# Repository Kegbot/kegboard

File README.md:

# Kegboard

Kegboard is the kegerator controller firmware from the [Kegbot][kegbot] project.
It reads flow meters, temperature sensors, and auth tokens, drives valves and
relays, and reports pours to a [Kegbot Server][kegbot-server].

This is **Kegboard v4**, a ground-up rewrite for **ESP32** built on
[ESPHome][esphome].

> **Looking for the Arduino version?** The v2/v3 firmware lives on the
> [`arduino`](https://github.com/Kegbot/kegboard/tree/arduino) branch. It is
> feature-frozen and does not speak the same protocol as this one.

**[📖 Documentation](https://docs.kegbot.org/projects/kegboard)** — overview,
operating modes, installation, wiring, configuration, and the protocol specs.
Sources in [`docs/`](docs/).

## What changed, and why

The old Kegboard was a dumb sensor pipe: it streamed raw tick counts over USB
serial, and a host daemon (`kegbot-pycore`) assembled those ticks into pours and
posted them to the server. That meant a cable, a always-on host, and a lost pour
whenever the host was down.

Kegboard v4 is a networked appliance:

- **Pours are assembled on the device.** The board detects the start and end
  of a pour, applies its own calibration, and reports a finished pour with an
  authoritative `volume_ml`.
- **One simple protocol.** Everything is JSON batches to a single endpoint
  (`POST /kegboard-event`), specified in
  [docs/kegboard-event-protocol.md](docs/kegboard-event-protocol.md) with
  normative JSON Schemas. Any server can implement it.
- **Outages are survivable.** Events queue and deliver late with correct
  timestamps — even on a board whose clock never synced — and retries can
  never create a duplicate drink.
- **No API keys to carry around.** An unprovisioned board shows up on the
  server dashboard by name; click allow and it provisions itself.
- **No `kegbot-pycore`, no USB cable.** WiFi and HTTP.
- **It's ESPHome.** Adding a display, a pressure sensor, a second thermometer,
  or a different RFID reader is YAML you write, not a firmware release we ship.

## Status

Early. Under active construction — see the table below.

| Area | State |
|---|---|
| Core logic (pour detection, event protocol, grants) | Done, unit tested |
| `kegboard` hub + `kegboard_meter` | Done |
| `kegboard_reporter` (event protocol, pairing, commands) | Done |
| `kegboard_auth` (server-decided grants, local mode) | Done |
| Temperature via stock `dallas_temp` | Works |
| Relays with watchdog, buzzer, flow LEDs | Done |
| Auth readers (RFID, iButton) | Done |
| Server implementing the protocol | In progress (kegbot-server) |
| Prebuilt binaries + web installer | Planned |

Nothing has been validated against real hardware and a live Kegbot Server yet.

Reporting is **HTTP only** for now. MQTT, BLE, and WebSocket transports are
planned.

## Configuration

A minimal two-tap board reporting to a server:

```yaml
external_components:
  - source: github://Kegbot/kegboard@main

kegboard:
  id: kb

kegboard_meter:
  - id: flow0
    pin: GPIO4
    index: 0
    total:
      name: Tap 1 Ticks
    pouring:
      name: Tap 1 Pouring

kegboard_reporter:
  reporting_url: !secret kegboard_reporting_url
  meters: [flow0]
```

See `examples/` for complete configs, and `boards/` for pin maps.

### `kegboard`

| Option | Default | Notes |
|---|---|---|
| `serial_number` | `kegboard-<mac>` | Device identity in the protocol. Set explicitly to adopt a replaced board's identity. |

### `kegboard_meter`

| Option | Default | Notes |
|---|---|---|
| `pin` | required | Meter input. Pulled up internally; counts falling edges. |
| `meter_number` | `0` | The protocol's meter number: `(device, meter_number)` identifies a tap server-side. Must be unique per meter (validated at build). The YAML `id` is a config-internal reference and is never reported. |
| `ml_per_tick` | `0.185` | SwissFlow SF800 and clones (~5.4 ticks/mL). The device's calibration is authoritative: reported volume comes from this. |
| `debounce` | `1200us` | Matches the legacy firmware's filter. |
| `idle_timeout` | `10s` | Silence after which a pour is considered finished. |
| `min_pour_ticks` | `3` | Anything shorter is treated as a drip and discarded. |
| `max_pour_duration` | `5min` | Safety cutoff for a stuck meter; `0s` disables. |
| `report_interval` | `250ms` | Throttle for sensor updates during a pour. |
| `series_resolution` | `100ms` | Bucket width for the diagnostic tick series; `0s` disables. |

Optional entities: `total`, `volume`, `flow_rate`, `pouring`.
Triggers: `on_pour_start`, `on_pour_end` (with `ticks`, `volume_ml`, `duration_ms`).
Actions: `kegboard_meter.reset_total`, `.end_pour`, `.set_calibration`.

### `kegboard_reporter`

Speaks the [Kegboard Event Protocol](docs/kegboard-event-protocol.md).

| Option | Default | Notes |
|---|---|---|
| `reporting_url` | required | Full URL, path included, e.g. `https://kegbot.example.com/api/kegboard-event`. No credential is configured — the device provisions its own bearer token by pairing via the server dashboard, and it persists in flash. |
| `meters` | `[]` | Meters whose pours are reported. |
| `thermo_sensors` | `[]` | `sensor:`/`name:` pairs; any ESPHome sensor works. |
| `heartbeat_interval` | `60s` | Status event cadence; also bounds worst-case command latency. |
| `pour_update_interval` | `1s` | Live `pour_update` cadence; `0s` disables. |
| `retry_interval` | `30s` | Base for exponential backoff, capped at 5 min. |

Optional diagnostic entities: `queue_depth`, `dropped`. A non-zero `dropped`
means events were lost and is worth alerting on.

### `kegboard_auth`

Applies [authenticated pouring](docs/authenticated-pouring.md): per-meter
grants, decided by the server (or locally), driving valve toggles and pour
attribution.

| Option | Default | Notes |
|---|---|---|
| `mode` | `server` | `server`: every token presentment is decided by the server, which chooses the meters, user, and duration. `local`: every token pours as guest, serverlessly. |
| `gates` | `[]` | `meter:` plus optional `toggle:` (valve relay). A gate without a toggle gets attribution only. |
| `offline_policy` | `deny` | Token presented while the server is unreachable: `deny`, or `guest` (attribution only — never opens valves). |
| `max_grant_duration` | `5min` | Device-side clamp on server-issued grants: the final bound on valve-open time. |
| `local_grant_duration` | `30s` | Grant length in `local` mode and for offline-guest grants. |

Actions: `kegboard_auth.token_attached` / `.token_detached` (`device`,
`token`), `.revoke`. Condition: `.is_authorized`. Triggers: `on_authorized`
(`user`), `on_denied` (`reason`), `on_revoked`. Optional entities:
`authorized`, `user`.

### `kegboard_onewire`

iButton presence on a 1-Wire bus — ESPHome's `one_wire` enumerates devices but
has no arrive/leave events. Triggers `on_token_attached` and
`on_token_detached` with the ROM code as hex.

`max_missed_searches` (default `4`) is how many consecutive misses before a
detach is reported. A held iButton makes intermittent contact, so reporting on
the first miss would make it flap several times a second.

### Relays and buzzer

`packages/relays.yaml` and `packages/buzzer.yaml` are plain YAML over stock
components. The relay watchdog is worth keeping from the AVR firmware: a relay
left on is usually a valve held open, so each one switches itself off after
`relay_watchdog_timeout` (default `10s`) unless something turns it on again.

## Repository layout

```
components/     ESPHome external components (this repo is the component source)
  kegboard/     Hub component + the framework-agnostic core (see CORE.md)
  kegboard_meter/     Flow meter and pour detection
  kegboard_reporter/  Event protocol client (batching, pairing, commands)
  kegboard_auth/      Per-meter authorization
  kegboard_onewire/   iButton presence
packages/       Composable YAML users include
boards/         Pin maps per target board
docs/           Manual + protocol specifications
schemas/        Normative JSON Schemas for the protocol
examples/       Worked configurations
tests/core/     Host unit tests -- plain g++, no hardware, no toolchain
script/         CI helpers
```

## Development

Host unit tests for the core logic need nothing but a C++ compiler:

```console
$ make -C tests/core
$ make -C tests/core STRICT=1   # warnings as errors, as CI runs it
```

Build output is scoped by OS and architecture (`build/Darwin-arm64/`, etc.), so
a checkout shared between a host and a container or VM won't hand one
platform's binaries to the other.

Formatting and lint mirror ESPHome's own conventions, since these components
compile into ESPHome's tree:

```console
$ pip install pre-commit && pre-commit install
$ pre-commit run --all-files
```

The manual is a Sphinx project in `docs/`, published at
[docs.kegbot.org/projects/kegboard](https://docs.kegbot.org/projects/kegboard).
Its toolchain is managed by [uv](https://docs.astral.sh/uv/), synced
automatically on first use:

```console
$ make -C docs html          # output in docs/_build/html/
$ make -C docs livehtml      # live-rebuild server while editing
```

## Simulator

`tools/kegboard-sim.py` is a TUI kegboard for developing receivers without
hardware. It speaks the full protocol — pairing, batching, `age_ms`,
commands, dedup — and validates every outgoing batch against the schemas, so
it cannot teach a server the wrong protocol.

```console
$ uv run tools/kegboard-sim.py http://localhost:8000/kegboard-event
```

Single keys drive it: pour a beer (with live `pour_update`s), toggle
temperature logging, present preset tokens (including an unknown fob and a
presence-style iButton), kill the heartbeat so your server's liveness check
can notice, go offline to build a backlog that delivers late with correct
ages, replay the last batch verbatim to exercise dedup, send an
unknown event type, and reboot to reset `boot_id`.

## Debugging

The reporter logs one line per delivery at `DEBUG` (status, event count,
bytes). To see the actual protocol traffic — every request and response body,
including `pour_update`s while beer is flowing — raise its log level to
`VERY_VERBOSE`:

```yaml
logger:
  logs:
    kegboard_reporter: VERY_VERBOSE
```

Then attach with `esphome logs <config>.yaml`. Two notes:

- `VERY_VERBOSE` lines are compiled out at default log levels, so production
  builds pay nothing for this machinery.
- The logger truncates lines to its buffer (default 512 bytes); a full batch
  body will clip. Add `logger: { tx_buffer_size: 2048 }` if that bites.

## Hardware notes

**ESP32 GPIOs are not 5 V tolerant.** Most beer flow meters are open-collector
hall-effect sensors, which are safe on a 3.3 V pull-up because they only ever
pull the line to ground. Meters with a push-pull 5 V output will damage the
ESP32 and need a level shifter or divider. Check your meter before wiring it.

## History

Kegboard was created in 2004 and has received several major updates over the
years:

- **v1 (2004)** — PIC16-based, written in the JAL programming language.
- **v2 (~2009)** — rewritten for Arduino, introducing the KBSP serial
  protocol.
- **v3 (2014)** — the Kegboard Pro Mini, a fully-assembled Arduino-based
  board.
- **v4 (2026)** — this ground-up ESP32 rewrite on ESPHome.

## License and copyright

Kegboard v4 is offered under the **MIT** license, matching the rest of the
Kegbot project; see `LICENSE.txt`.

Two notes on what that does and doesn't cover:

- **Built firmware images are GPLv3.** ESPHome's C++ runtime is GPLv3, and a
  compiled Kegboard image links against it. MIT is GPL-compatible, so this is
  fine and is how ESPHome external components normally work — but if you
  distribute binaries, you are distributing GPLv3 binaries. The source in this
  repository remains MIT and is reusable as such.
- **The `arduino` branch is still GPLv2-or-later.** The legacy AVR firmware was
  written under that license and had outside contributors; nothing here
  relicenses it.

Copyright 2003-2026 The Kegbot Project Contributors <info@kegbot.org>

[kegbot]: https://kegbot.org/
[kegbot-server]: https://github.com/Kegbot/kegbot-server
[esphome]: https://esphome.io/

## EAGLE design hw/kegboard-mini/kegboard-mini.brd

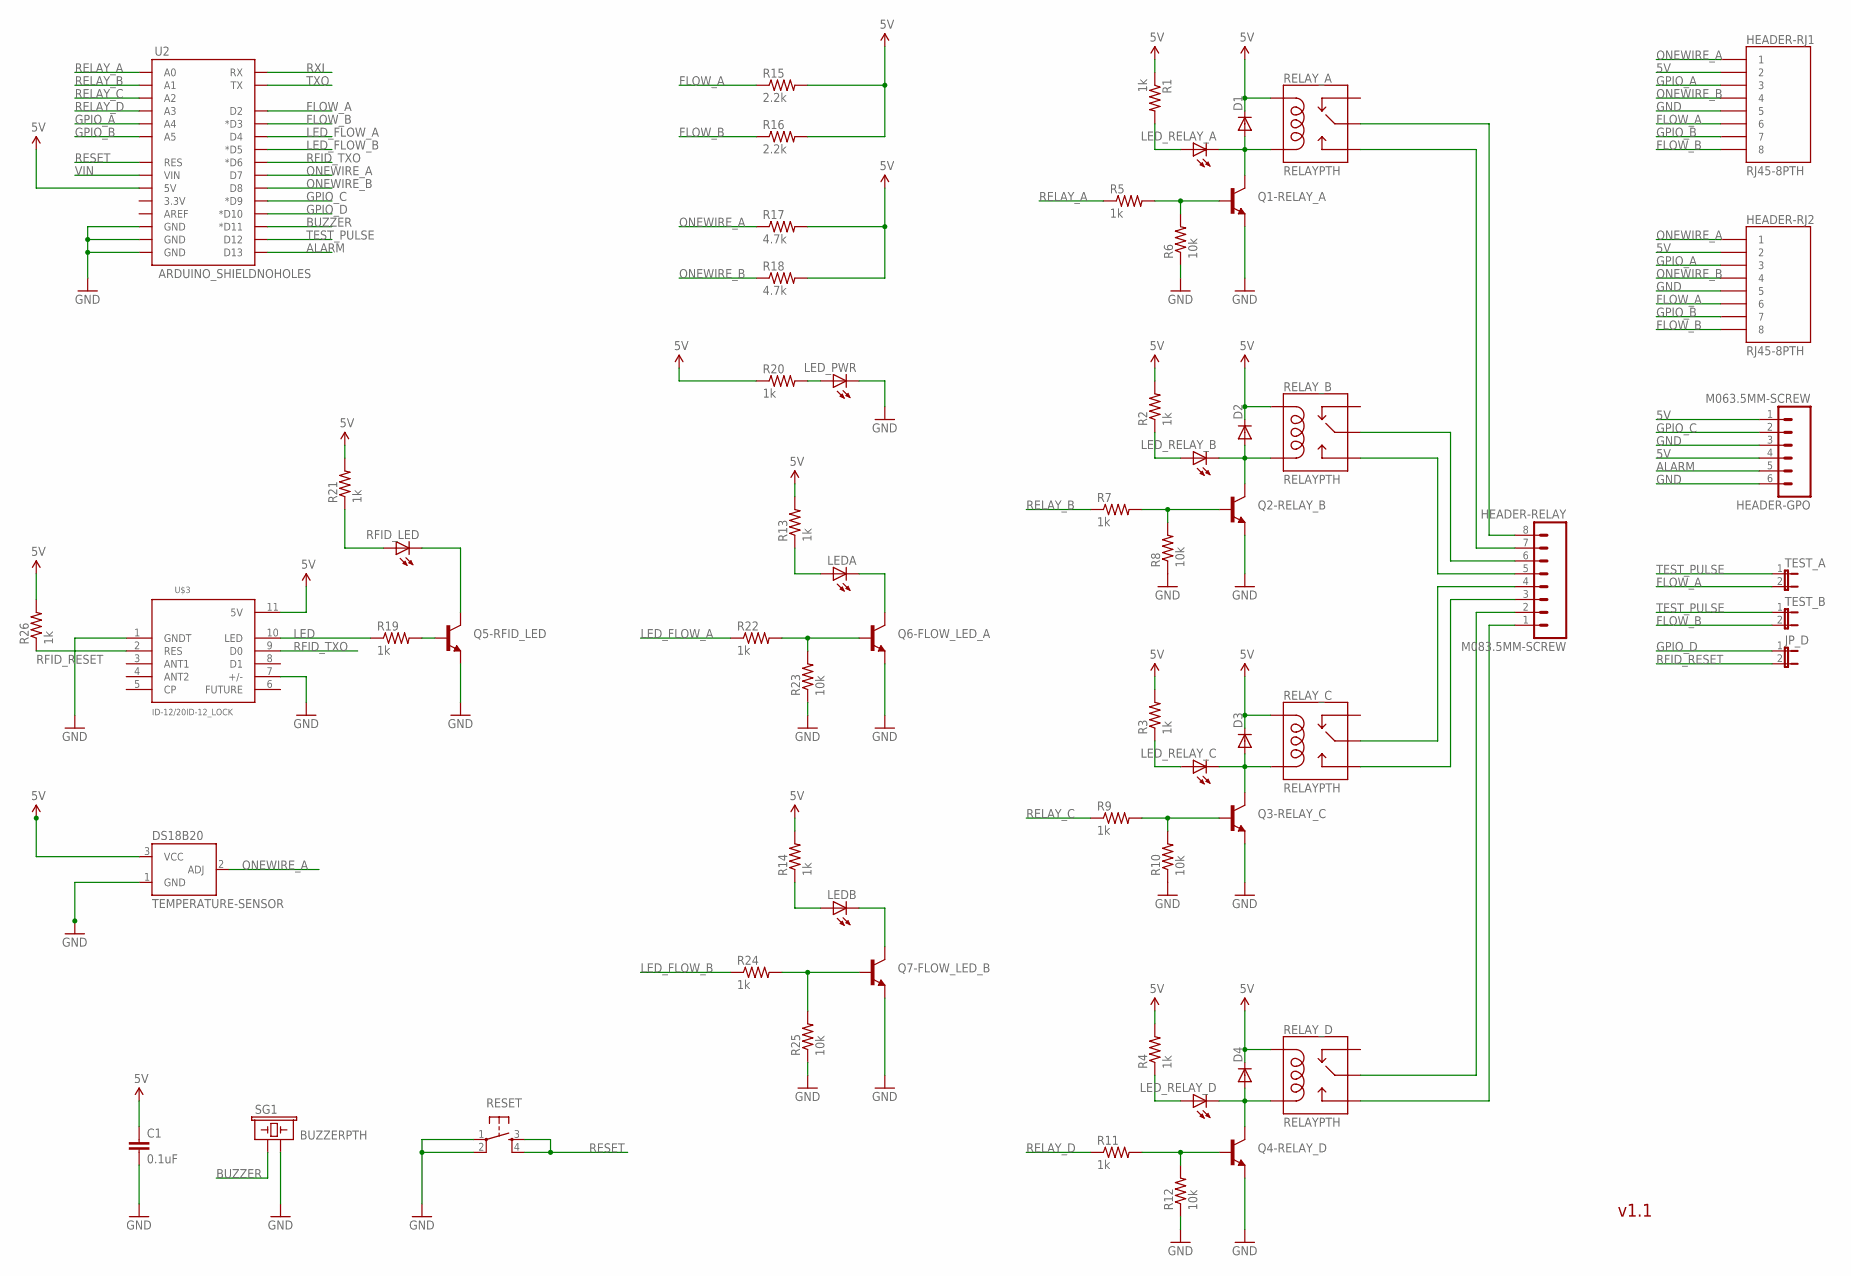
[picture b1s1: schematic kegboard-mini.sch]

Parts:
C1: 0.1uF; CAP-PTH-SMALL
D1, D2, D3, D4: DIODE1N4148; DIODE-1N4148
DS18B20: TEMPERATURE-SENSOR; TO-92
HEADER-GPO: M063.5MM-SCREW; SCREWTERMINAL-3.5MM-6
HEADER-RELAY: M083.5MM-SCREW; SCREWTERMINAL-3.5MM-8
HEADER-RJ1, HEADER-RJ2: RJ45-8PTH; RJ45-8
JP_D: JUMPER-2PTH; 1X02
LEDA: LED3MM
LEDB: LED3MM
LED_PWR: LED3MM
LED_RELAY_A: LED3MM
LED_RELAY_B: LED3MM
LED_RELAY_C: LED3MM
LED_RELAY_D: LED3MM
Q1-RELAY_A, Q2-RELAY_B, Q3-RELAY_C, Q4-RELAY_D, Q5-RFID_LED, Q6-FLOW_LED_A, Q7-FLOW_LED_B: TRANSISTOR_NPNTO92; TO-92
R1, R2, R3, R4, R5, R7, R9, R11, R13, R14, R19, R20, R21, R22, R24, R26: 1k; AXIAL-0.3
R6, R8, R10, R12, R23, R25: 10k; AXIAL-0.3
R15, R16: 2.2k; AXIAL-0.3
R17, R18: 4.7k; AXIAL-0.3
RELAY_A: RELAYPTH; RELAY-G5Q
RELAY_B: RELAYPTH; RELAY-G5Q
RELAY_C: RELAYPTH; RELAY-G5Q
RELAY_D: RELAYPTH; RELAY-G5Q
RESET: TAC_SWITCHPTH; TACTILE-PTH
RFID_LED: LED3MM
SG1: BUZZERPTH; BUZZER-12MM
TEST_A: JUMPER-2PTH; 1X02
TEST_B: JUMPER-2PTH; 1X02
U2: ARDUINO_SHIELDNOHOLES; DUEMILANOVE_SHIELD_NOHOLES
U$3: ID-12/20ID-12_LOCK; ID-12_LOCK

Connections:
5V: C1.1, D1.C, D2.C, D3.C, D4.C, DS18B20.3 (VCC), HEADER-GPO.1, HEADER-GPO.4, HEADER-RJ1.2, HEADER-RJ2.2, R1.P$1 (1), R2.P$2 (2), R3.P$2 (2), R4.P$2 (2), R13.P$2 (2), R14.P$2 (2), R15.P$2 (2), R16.P$2 (2), R17.P$2 (2), R18.P$2 (2), R20.P$1 (1), R21.P$2 (2), R26.P$2 (2), RELAY_A.5 (COIL1), RELAY_B.5 (COIL1), RELAY_C.5 (COIL1), RELAY_D.5 (COIL1), U2.5V, U$3.11 (5V)
ALARM: HEADER-GPO.5, U2.D13
BUZZER: SG1.+ (1), U2.D11 (*D11)
FLOW_A: HEADER-RJ1.6, HEADER-RJ2.6, R15.P$1 (1), TEST_A.2, U2.D2
FLOW_B: HEADER-RJ1.8, HEADER-RJ2.8, R16.P$1 (1), TEST_B.2, U2.D3 (*D3)
GND: C1.2, DS18B20.1 (GND), HEADER-GPO.3, HEADER-GPO.6, HEADER-RJ1.5, HEADER-RJ2.5, LED_PWR.K (C), Q1-RELAY_A.1 (E), Q2-RELAY_B.1 (E), Q3-RELAY_C.1 (E), Q4-RELAY_D.1 (E), Q5-RFID_LED.1 (E), Q6-FLOW_LED_A.1 (E), Q7-FLOW_LED_B.1 (E), R6.P$1 (1), R8.P$1 (1), R10.P$1 (1), R12.P$1 (1), R23.P$1 (1), R25.P$1 (1), RESET.1, RESET.2, SG1.- (2), U2.GND@0 (GND), U2.GND@1 (GND), U2.GND@2 (GND), U$3.1 (GNDT), U$3.7 (+/-)
GPIO_A: HEADER-RJ1.3, HEADER-RJ2.3, U2.A4
GPIO_B: HEADER-RJ1.7, HEADER-RJ2.7, U2.A5
GPIO_C: HEADER-GPO.2, U2.D9 (*D9)
GPIO_D: JP_D.1, U2.D10 (*D10)
LED: R19.P$1 (1), U$3.10 (LED)
LED_FLOW_A: R22.P$1 (1), U2.D4
LED_FLOW_B: R24.P$1 (1), U2.D5 (*D5)
unnamed: LED_RELAY_A.A, R1.P$2 (2)
unnamed: Q2-RELAY_B.2 (B), R7.P$2 (2), R8.P$2 (2)
unnamed: Q1-RELAY_A.2 (B), R5.P$2 (2), R6.P$2 (2)
unnamed: Q3-RELAY_C.2 (B), R9.P$2 (2), R10.P$2 (2)
unnamed: LED_RELAY_C.A, R3.P$1 (1)
unnamed: Q4-RELAY_D.2 (B), R11.P$2 (2), R12.P$2 (2)
unnamed: LED_RELAY_B.A, R2.P$1 (1)
unnamed: LEDB.K (C), Q7-FLOW_LED_B.3 (C)
unnamed: LEDA.K (C), Q6-FLOW_LED_A.3 (C)
unnamed: D1.A, LED_RELAY_A.K (C), Q1-RELAY_A.3 (C), RELAY_A.1 (COIL2)
unnamed: LED_RELAY_D.A, R4.P$1 (1)
unnamed: D2.A, LED_RELAY_B.K (C), Q2-RELAY_B.3 (C), RELAY_B.1 (COIL2)
unnamed: LED_PWR.A, R20.P$2 (2)
unnamed: D3.A, LED_RELAY_C.K (C), Q3-RELAY_C.3 (C), RELAY_C.1 (COIL2)
unnamed: HEADER-RELAY.8, RELAY_A.2 (MAIN)
unnamed: D4.A, LED_RELAY_D.K (C), Q4-RELAY_D.3 (C), RELAY_D.1 (COIL2)
unnamed: Q5-RFID_LED.2 (B), R19.P$2 (2)
unnamed: R21.P$1 (1), RFID_LED.A
unnamed: Q5-RFID_LED.3 (C), RFID_LED.K (C)
unnamed: HEADER-RELAY.7, RELAY_A.3 (NO)
unnamed: HEADER-RELAY.6, RELAY_B.2 (MAIN)
unnamed: HEADER-RELAY.5, RELAY_B.3 (NO)
unnamed: HEADER-RELAY.4, RELAY_C.2 (MAIN)
unnamed: LEDA.A, R13.P$1 (1)
unnamed: HEADER-RELAY.3, RELAY_C.3 (NO)
unnamed: HEADER-RELAY.2, RELAY_D.2 (MAIN)
unnamed: HEADER-RELAY.1, RELAY_D.3 (NO)
unnamed: LEDB.A, R14.P$1 (1)
unnamed: Q6-FLOW_LED_A.2 (B), R22.P$2 (2), R23.P$2 (2)
unnamed: Q7-FLOW_LED_B.2 (B), R24.P$2 (2), R25.P$2 (2)
ONEWIRE_A: DS18B20.2 (ADJ), HEADER-RJ1.1, HEADER-RJ2.1, R17.P$1 (1), U2.D7
ONEWIRE_B: HEADER-RJ1.4, HEADER-RJ2.4, R18.P$1 (1), U2.D8
RELAY_A: R5.P$1 (1), U2.A0
RELAY_B: R7.P$1 (1), U2.A1
RELAY_C: R9.P$1 (1), U2.A2
RELAY_D: R11.P$1 (1), U2.A3
RESET: RESET.3, RESET.4, U2.RES
RFID_RESET: JP_D.2, R26.P$1 (1), U$3.2 (RES)
RFID_TXO: U2.D6 (*D6), U$3.9 (D0)
RXI: U2.RX
TEST_PULSE: TEST_A.1, TEST_B.1, U2.D12
TXO: U2.TX
VIN: U2.VIN

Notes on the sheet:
v1.1

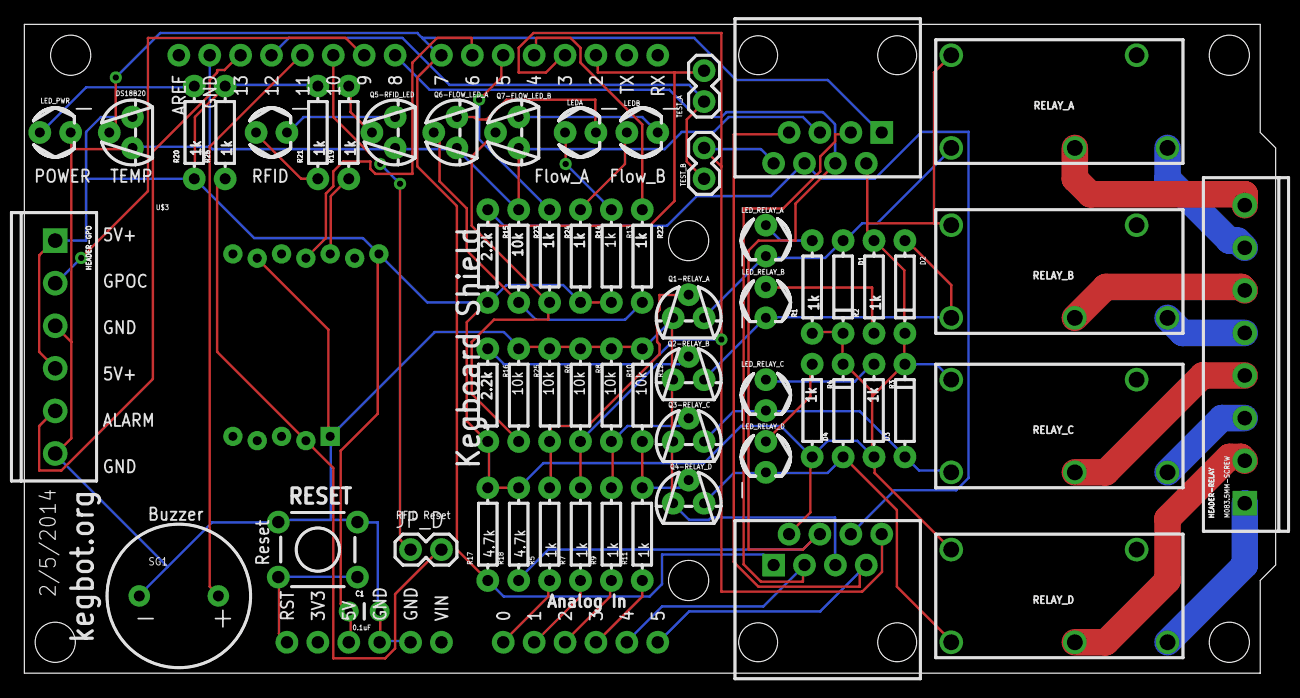
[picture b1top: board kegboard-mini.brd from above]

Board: 2 copper layers, 102.9 x 53.3 mm, 68 parts (0 on the bottom side), 53 nets.

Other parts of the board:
JP1, JP2, JP3, JP4, JP5, JP6: STAND-OFF

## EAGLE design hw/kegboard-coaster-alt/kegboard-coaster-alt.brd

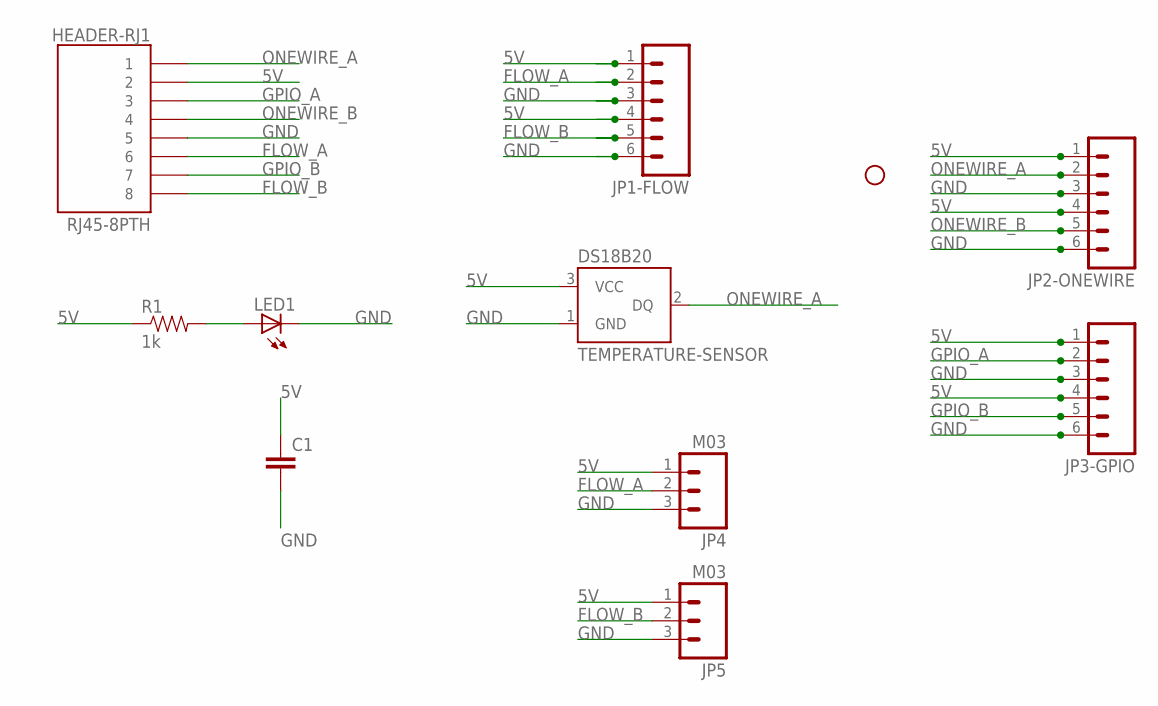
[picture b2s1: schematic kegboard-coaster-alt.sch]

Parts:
C1: CAPPTH2; CAP-PTH-SMALL2
HEADER-RJ1: RJ45-8PTH; RJ45-8
JP1-FLOW, JP2-ONEWIRE, JP3-GPIO: M063.5MM-6; SCREWTERMINAL-3.5MM-6
JP2: STAND-OFF
JP4, JP5: M03; 53324-0360
LED1: LED3MM
R1: 1k; AXIAL-0.3
U$1: TEMPERATURE-SENSOR; TO-92

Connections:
5V: C1.1, HEADER-RJ1.2, JP1-FLOW.1, JP1-FLOW.4, JP2-ONEWIRE.1, JP2-ONEWIRE.4, JP3-GPIO.1, JP3-GPIO.4, JP4.1, JP5.1, R1.P$1 (1), U$1.3 (VCC)
FLOW_A: HEADER-RJ1.6, JP1-FLOW.2, JP4.2
FLOW_B: HEADER-RJ1.8, JP1-FLOW.5, JP5.2
GND: C1.2, HEADER-RJ1.5, JP1-FLOW.3, JP1-FLOW.6, JP2-ONEWIRE.3, JP2-ONEWIRE.6, JP3-GPIO.3, JP3-GPIO.6, JP4.3, JP5.3, LED1.K (C), U$1.1 (GND)
GPIO_A: HEADER-RJ1.3, JP3-GPIO.2
GPIO_B: HEADER-RJ1.7, JP3-GPIO.5
unnamed: LED1.A, R1.P$2 (2)
ONEWIRE_A: HEADER-RJ1.1, JP2-ONEWIRE.2, U$1.2 (DQ)
ONEWIRE_B: HEADER-RJ1.4, JP2-ONEWIRE.5

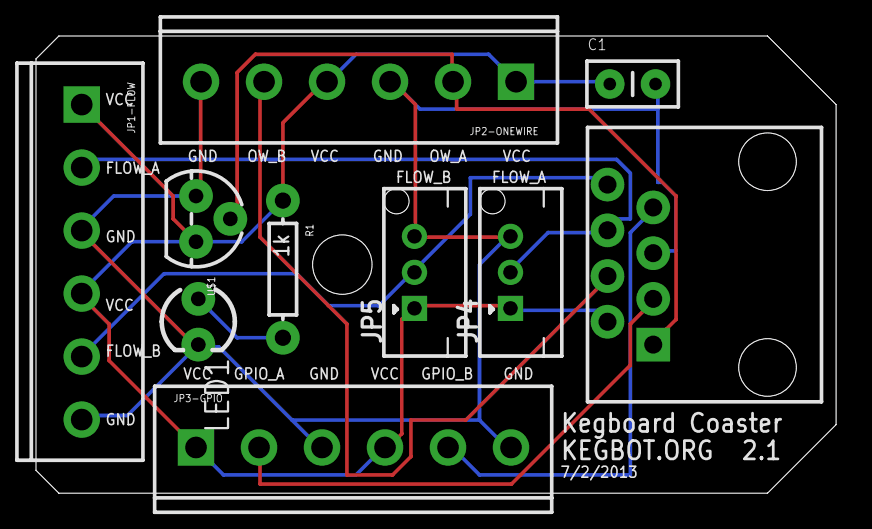
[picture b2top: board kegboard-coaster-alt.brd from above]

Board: 2 copper layers, 44.5 x 25.4 mm, 11 parts (0 on the bottom side), 9 nets.

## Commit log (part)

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2002-05-28 initial checkin
2006-04-02 - add kegboard source
2006-04-03 - adding original rs232_hw jal file, from: http://oase.uci.kun.nl/~mientki/pic/libs_hw/rs232_hw.html
    needs some modification to work with jpic registe defines
2006-04-03 - cleaned up kegboard.jal - added jpic comptabile pin/register definitions -- I must have inherited a bunch of weird naming conventions from JALss - added a Makefile
2006-04-03 - add Philip Pemberton's 1wire.jal library
2006-04-03 - deleting; accidentally submitted changed version
2006-04-03 - update to use jdelay (more portable)
2006-04-03 - added temperature support!
2006-04-03 - update to constantly push status (1x/second in normal case, 5x/second in flow) - added some untested procedures for printing as ascii :)
2006-04-03 - added init message
2006-04-04 - added human-readable output for all fields in the status packet! - changed command names to all be (a) a single ascii char, and (b) intuitive (ie 'F' to enable fridge, 'f' to disable) - TODO: board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
2012-03-31 Add option to force-set HUPCL on the serial port. Source: http://www.arduino.cc/cgi-bin/yabb2/YaBB.pl?num=1201441300
2012-03-31 Revert default baud rate to 115200bps.
2012-03-31 Add TODO.
2012-03-31 Many enhancements to kegboard3.
    - adds onewire support
    - created a non-delay()ing wrapper for ds18*20 sensors
    - temperature conversion now supported
    - adds start of TLV eeprom storage. untested, compiles.
    - many todos and cleanups remain
2012-03-31 Better idea: don't mess with HUPCL, instead just set the rate to 0.
2012-03-31 Add CRC-CCITT (Xmodem) checksum of flow data.
2012-03-31 Add command line makefile.
2012-03-31 Fix up Makefile defaults.
2012-03-31 Move hardware controller code out of pykeg.
2012-03-31 Enable weak internal pullups on flow pins.
2012-03-31 Kegboard updates: new command format, start handling rx commands.
    Still a work in progress.
2012-03-31 Rename project file to make arduino ide happy.
2012-03-31 Increase responsiveness of the main loop.
    This change removes the delay in the main loop; as a result, some operations are
    noticably more responsibe (eg OneWire presence events). Searches happen much
    more frequently as well.
    Changes selftest to report on a set interval (every 500ms), making it
    easier to use in testing situations.
2012-03-31 Fix serial packet output (missing preamble).
2012-03-31 Add 1-wire presence detect to kegboard; rework temperature sensing.
    Details:
    - One bus is now dedicated to temperature sensor (and no longer operates in
    onewire 'skip' mode); the other is now used for presence events.
    - A new KBSP message has been added for presence events, and pykeg side has
    been updated to parse this message. (Auth support for kegboard_daemon to be
    added later.)
2012-03-31 Move buzzer.c -> buzzer.cpp
2012-03-31 Fix temperature conversion.
    Add protocol version.
2012-03-31 Fix bug in OneWire::search.
    The condition where a device disappears mid-search was not handled correctly; as
    a result, a button removed mid search could end up being reported indefinitely.
    This could be easily reproduced by repeatedly searching & wiggling the iButton
    device physically on and off the bus.
    Misc whitespace/style cleanups.
2012-03-31 Snapshot of initial support for receiving command packets. Not yet tested.
2012-03-31 Remove dead eeprom code. Reimplement this later. Allocate pin for buzzer.
2012-03-31 Bug fix for onewire changes.
    Also adds support for DS18S20 temperature sensor.
2012-03-31 Fix build when OneWire is disabled (thanks Andrew!)
2012-03-31 DS1820 bugfix: Do not report '0' for a sensor that disappears mid-read.
2012-03-31 Print avr-size after building elf.
2012-03-31 Rename kegboard source tree to satisfy the wacky arduino IDE.
    Resolves issue #6.
2012-03-31 Whitespace cleanup.
2012-03-31 Fix CRC'ing of KBSP packets.
2012-03-31 Fix broken melody note.
2012-03-31 Whitespace/style cleanups.
2012-03-31 Initial support for Matrix-Orbital serial LCDs; rx packet bugfixes.
2012-03-31 Move boot melody data to PROGMEM, saving a few dozen bytes.
    Code and data sizes have significantly shrunk thanks to the past few
    optimizations.
    Output of /usr/bin/avr-size -C --mcu=atmega168 build-cli/kegboard-v3.elf
    At revision 602:
    AVR Memory Usage
    ----------------
2012-03-31 Kegboard: Experimental change to cache onewire device presence and report device absence.
    Written without access to AVR: needs to be tested. Also need update to kegboard
    daemon due to changed semantics of presence packet.
2012-03-31 Move buzzer constants to progrem memory, saving a few dozen bytes of RAM.
2012-03-31 Fix stupid offset error.
2012-03-31 Remove the global KegboardPacket used for serial output; instead, create it on demand.
2012-03-31 Change protocol_version field to firmware_version; set initial version to 4.
2012-03-31 Add relay on/off command support; clean up types.
2012-03-31 Small optimizations.
    - Compute crc inline while printing a packet.
    - Refactor handling of multi-byte integer values.
2012-03-31 Recover over 200 bytes of program data by removing _delay_ms.
    Also removes MelodyNote structure, to simplify storing melodies with PROGMEM.
2012-03-31 Update to kegboard firmware v5. Fixes issue with excessive tick reporting.
2012-03-31 Clean up onewire search to better match appnote flow chart.
    Check CRC before returning results.
2012-03-31 Fix status reporting.
2012-03-31 Use SoftwareSerial.
2012-03-31 kegboard-coaster: update pin breakouts.
2012-03-31 First draft of arduino carrier board (Eagle project files.)
2012-03-31 Update with changes from geoff culp (geoffculp@gmail.com).
2012-03-31 Update shield design.
    Changes:
    - now sized for / compatible with Arduino MEGA
    - supports up to 6 flow inputs
    - up to 6 RJ45 sockets
    - 4 output relay blocks
    - 4 general purpose output terminal blocks
2012-03-31 coaster: tweaks to layout; autorouted.
2012-03-31 First attempt at routing the relay section.
2012-03-31 Board updates; see ChangeLog.
2012-03-31 kegboard-coaster: tweaking things (see changelog)
2012-03-31 kegboard-mini: initial routing.
2012-03-31 Update to work with arduino-0018.
    Resolves issue #37.
2012-03-31 Add missing include.
2012-03-31 Update board and schematic.
2012-03-31 Split kegboard shield projects into "mega" and "mini" versions.
    The "mini" version is copied from kegboard.{brd,sch} at hg revision 794. The
    existing kegboard.{brd,sch} have been moved to kegboard-mega.{brd,sch}.
2012-03-31 kegboard: disable serial lcd by default.
2012-03-31 kegboard: various pcb board layout changes, see change log for details.
2012-03-31 kegboard: fix build error with arduino-0022 (issue #77).
    (thanks jared)
2012-03-31 kegboard: add the auth_token message.
    The new message type is similar to the existing `onewire_presence` message, but
    adds an additional string field for the auth device name.
    This should make it possible to add report new types of auth tokens from
    kegboard (eg rfid, magstripe) without needing to define a new message or change
    kegboard daemon.
2012-03-31 kegboard: remove dash from relay names for consistency with meters.
2012-03-31 kegboard: (hopefully final) updates & routing before initial production.
    Changes:
    - Removed XBee components, replaced with ID-20/ID-12 RFID sensor. I decided
    (or rather guessed) that the RFID sensor would be a more popular choice, and
    the XBee can probably be supported with an additional stackable shield.
    Like the XBee, this component is optional.
    - Moved the RJ-45 jacks to the back-left edge, rather than opposing back
2012-03-31 kegboard: Expand 'set_output' to support onboard kegboard relay's, flow led's
2012-03-31 kegboard: minor cleanup to makefile.
2012-03-31 kegboard: bump firmware version to 6.
2012-03-31 kegboard: update schematic.
    Changes:
    - Remove notch from upper left corner (thanks geoffc).
    - Add drill hole for arduino uno; rearrange and re-route a few components to
    accomodate (thanks geoffc).
    - Rerouted a trace that had been autorouted too close to the relay rails.
2012-03-31 Arduino.mk: update to version 0.4; add notice.
2012-03-31 kegboard: Add NewSoftSerial library.
2012-03-31 kegboard fw: s/KB_MESSAGE_TYPE/KBM/g
2012-03-31 kegboard: coaster updates (1/23 version)
2012-03-31 kegboard fw: trivial changes.
2012-03-31 Adding support for magnetic stripe cards and pin change interrupts
2012-03-31 kegboard: fix bug in previous commit.
    (Don't play the melody for disapperances.)
2012-03-31 Kegboard: Alternate coaster design. Larger pcb board size for screw terminals.
2012-03-31 Fix errant ifdef
2012-03-31 kegboard: add logo and bump date.
2012-03-31 kegboard: reverse ID12 endianness to match other readers; bump to fw v10.
2012-03-31 NewSoftSerial: convert to unix file format.
2012-03-31 kegboard: bump to fw version 9; update docs.
2012-03-31 kegboard: 8/8/2011 revision, with logo
2012-03-31 Reorganize as standalone package.
2012-03-31 kegboard: play melody *after* emitting auth packet.
    Melody playback uses delay(). That should be fixed, but in the meantime do the
    "real" work first.
2012-05-03 Rename kegboard.pde -> kegboard.ino for Arduino 1.0
2012-05-03 Update for Arduino SDK v1.0. Bump to rev 11.
2012-07-01 Rename src/ to arduino/
2012-07-02 Move Kegboard Python code into kegboard repository.
    New package is called "kegbot-kegboard".
    Origin:
    URL: https://github.com/Kegbot/kegbot
    Commit: a0fc59b9257eb6ff247ba4ff54b1180a675f13bb
2012-07-02 Add makefile
2012-07-09 Play a short tone on ping; bump to rev 12.
2012-07-09 Try a few more common default devices.
2012-07-10 Arduino-Makefile: update tools to use `/usr/bin/env perl`
2012-07-10 Update gitignore.
2012-07-11 arduino: experimental support for wiegand RFID readers.
    Currently returns the raw wiegand value (including any parity bits).
2012-08-23 Add docs (moved from kegbot server repository)
2012-10-05 Add PDF board and schematic files.
2012-10-29 docs: add changelog; bump fw to v13
2013-02-23 Fix typo in 'authentication'.
2013-04-04 Fixed url for Kegboard
    Not sure if the url is broken, been updated, or if it was just a typo…
2013-04-30 Arduino: replace makefile with http://ed.am/dev/make/arduino-mk
2013-04-30 firmware: add experimental software debounce.
    Suspected EMI transients have been observed spuriously triggering the
    external interrupt lines on some systems. Likely this is better solved
    in hardware, however this is not as convenient as a software fix.
    When enabled, ISRs first delay by a fixed about (~1.2ms currently) and
    then inspects the active-low interrupting pin. The delay amount
    was selected somewhat empirically (with a non-SF800 sensor) and
2013-05-01 added parallax.h and parall.cpp files
2013-05-08 hw: coaster (alt): add headers for molex 53324-0360 connector.
2013-07-22 add support for parallax RFID
2013-07-22 ensure only one RFID system enabled
2013-07-23 Firmware v14
2013-10-23 Update kegboard.ino
    Added a few lines to reset the WIEGAND reader so the first read is correct and doesn't require two scans initially
2014-01-11 Don't compile buzzer.o when disabled.
    Should be done in the build system, but the Arduino IDE
    is dumb.
2014-01-11 buzzer: Update to use Arduino tone() library.
    Closes #3.
2014-01-11 Update boot melody.
2014-01-18 Add EEPROM serial number.
2014-01-18 Firmware v15
2014-01-18 Shorten boot melody.
2014-01-21 Add EEPROM.h to sketch (to satisfy broken Arduino IDE).
2014-01-28 Add support for pulsating chip LED.
2014-01-28 python: Add convenience methods; add kegboard-info.py
2014-02-05 kegboard-mini: Clean up board labels, no functional changes; bump to v1.0.1.
2014-02-06 Clean up Arduino firmware build.
    Enables -Werror on first-party code. Removes Magstripe
    due to compile errors and lack of use (will add it
    back if someone cleans it up).
2014-02-06 KBPM: Flash RX/TX LEDs in lieu of dedicated flow LEDs.
    (Only when serial is disconnected).
2014-02-07 Firmware v16.
2014-02-09 Move exceptions to own module.
2014-02-12 Fix misplaced cast that was breaking Uno/Mega.
    Also a few other warning-related cleanups.
2014-02-12 Firmware v17
2014-03-20 docs: Updates for Kegboard Pro Mini.
2014-04-30 Don't catch non-ping messages.
2014-04-30 v1.1.3
2014-04-30 Add Kegboard.wait_for_ping().
2014-05-14 Add heartbeat: ping the host every 10s.
2014-05-14 Include uptime information in Hello message.
2014-12-20 python: Respect glob_paths in `wait_for_kegboard`.
2014-12-20 v1.1.5
